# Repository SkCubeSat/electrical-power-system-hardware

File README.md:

# electrical-power-system-hardware

see branch 'master' for hardware design files

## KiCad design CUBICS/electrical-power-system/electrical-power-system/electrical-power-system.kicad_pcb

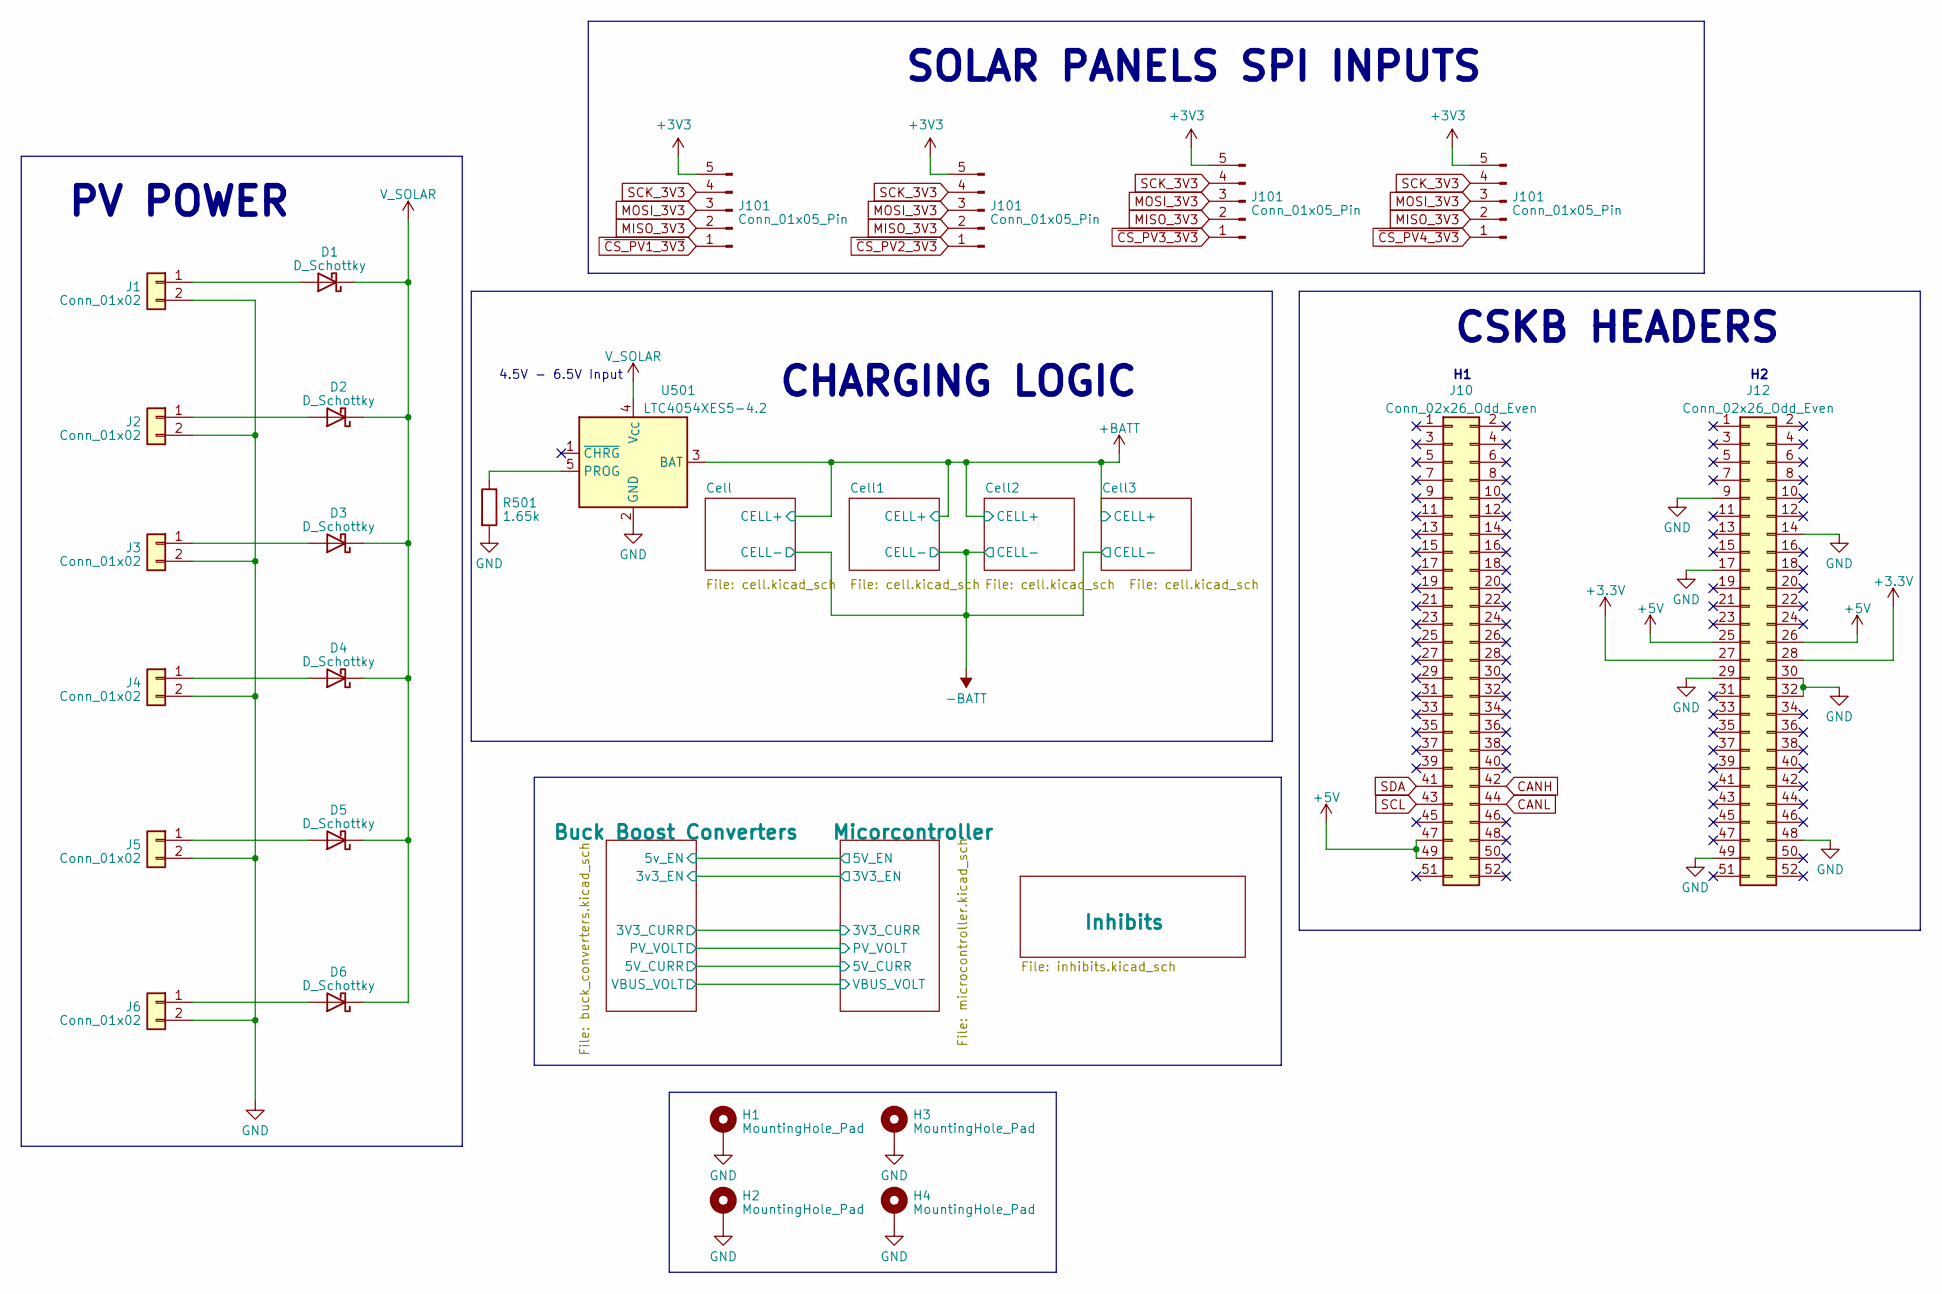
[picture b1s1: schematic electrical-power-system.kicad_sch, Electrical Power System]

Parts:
D1, D2, D3, D4, D5, D6: D_Schottky; D_A-405_P10.16mm_Horizontal
H1, H2, H3, H4: MountingHole_Pad; MountingHole_3.2mm_M3_ISO7380_Pad_TopBottom
J1, J2, J3, J4, J5, J6: Conn_01x02; PinHeader_1x02_P2.54mm_Vertical
J10, J12: Conn_02x26_Odd_Even; PinSocket_2x26_P2.54mm_Vertical
J101: Conn_01x05_Pin; Hirose_DF13-05P-1.25DSA_1x05_P1.25mm_Vertical
R501: 1.65k; R_0603_1608Metric
U501: LTC4054XES5-4.2; TSOT-23-5

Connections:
+1V2: D1.1 (K), D2.1 (K), D3.1 (K), D4.1 (K), D5.1 (K), D6.1 (K); also elsewhere on the board
+3.3V: J12.27, J12.28; also elsewhere on the board
+5V: J10.47, J10.49, J12.25, J12.26; also elsewhere on the board
CANH: J10.42; also elsewhere on the board
CANL: J10.44; also elsewhere on the board
GND: H1.1, H2.1, H3.1, H4.1, J1.2, J2.2, J3.2, J4.2, J5.2, J6.2, J12.9, J12.14, J12.17, J12.29, J12.30, J12.32, J12.48, J12.49; also elsewhere on the board
unnamed: D1.2 (A), J1.1
unnamed: D2.2 (A), J2.1
unnamed: D3.2 (A), J3.1
unnamed: D4.2 (A), J4.1
unnamed: D5.2 (A), J5.1
unnamed: D6.2 (A), J6.1
SCL: J10.43; also elsewhere on the board
SDA: J10.41; also elsewhere on the board

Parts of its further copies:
J7, J8, J9, J11: Conn_01x05_Pin; Hirose_DF13-05P-1.25DSA_1x05_P1.25mm_Vertical
R1: 1.65k; R_0603_1608Metric
U1: LTC4054XES5-4.2; TSOT-23-5

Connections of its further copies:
+1V2: U1.4 (V_{CC}); also elsewhere on the board
+3V3: J7.5, J8.5, J9.5, J11.5; also elsewhere on the board
+BATT: U1.3 (BAT); also elsewhere on the board
GND: R1.2, U1.2 (GND); also elsewhere on the board
MISO_3V3: J7.2, J8.2, J9.2, J11.2; also elsewhere on the board
MOSI_3V3: J7.3, J8.3, J9.3, J11.3; also elsewhere on the board
unnamed: R1.1, U1.5 (PROG)
SCK_3V3: J7.4, J8.4, J9.4, J11.4; also elsewhere on the board
~CS_PV1_3V3: J7.1; also elsewhere on the board
~CS_PV2_3V3: J8.1; also elsewhere on the board
~CS_PV3_3V3: J9.1; also elsewhere on the board
~CS_PV4_3V3: J11.1; also elsewhere on the board

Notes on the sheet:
PV POWER
CSKB HEADERS
4.5V - 6.5V Input
SOLAR PANELS SPI INPUTS
CHARGING LOGIC

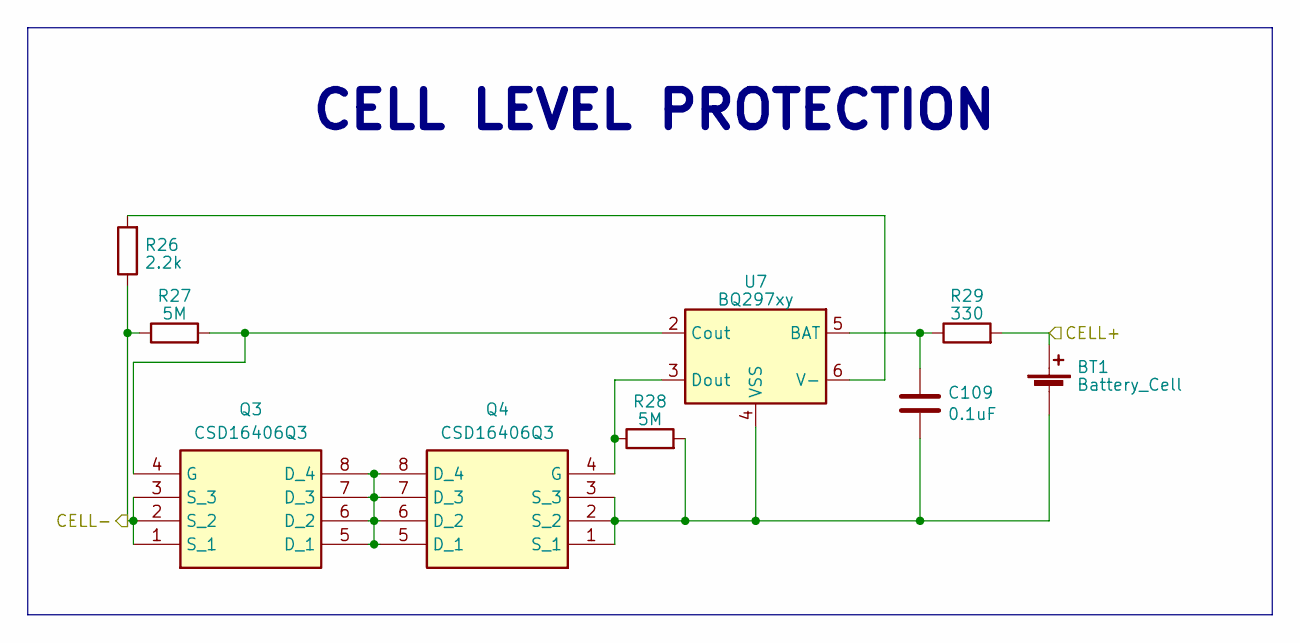
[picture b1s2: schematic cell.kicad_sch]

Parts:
BT1: Battery_Cell; 18650_TH
C109: 0.1uF; C_0603_1608Metric
Q3, Q4: CSD16406Q3; DQG_VSON-CLIP; Manufacturer_Part_Number CSD16406Q3; Mouser Part Number 595-CSD16406Q3
R26: 2.2k; R_0603_1608Metric
R27, R28: 5M; R_0603_1608Metric
R29: 330; R_0603_1608Metric
U7: BQ297xy; WSON-6_1.5x1.5mm_P0.5mm

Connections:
+BATT: BT1.1 (+), R29.2; also elsewhere on the board
-BATT: Q3.1 (S_1), Q3.2 (S_2), Q3.3 (S_3), R26.1, R27.1; also elsewhere on the board
unnamed 19: BT1.2 (-), Q4.1 (S_1), Q4.2 (S_2), Q4.3 (S_3), R28.2, U7.4 (VSS); also elsewhere on the board
unnamed: Q3.5 (D_1), Q3.6 (D_2), Q3.7 (D_3), Q3.8 (D_4), Q4.5 (D_1), Q4.6 (D_2), Q4.7 (D_3), Q4.8 (D_4)
unnamed: Q3.4 (G), R27.2, U7.2 (Cout)
unnamed: Q4.4 (G), R28.1, U7.3 (Dout)
unnamed 73: R29.1, U7.5 (BAT); also elsewhere on the board
unnamed: R26.2, U7.6 (V-)

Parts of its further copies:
BT2, BT3, BT4: Battery_Cell; 18650_TH
C25, C26, C27, C28: 0.1uF; C_0603_1608Metric
Q5, Q6, Q7, Q8, Q9, Q10: CSD16406Q3; DQG_VSON-CLIP; Manufacturer_Part_Number CSD16406Q3; Mouser Part Number 595-CSD16406Q3
R30, R34, R38: 2.2k; R_0603_1608Metric
R31, R32, R35, R36, R39, R40: 5M; R_0603_1608Metric
R33, R37, R41: 330; R_0603_1608Metric
U8, U9, U10: BQ297xy; WSON-6_1.5x1.5mm_P0.5mm

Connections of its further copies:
+BATT: BT2.1 (+), BT3.1 (+), BT4.1 (+), R33.2, R37.2, R41.2; also elsewhere on the board
-BATT: Q5.1 (S_1), Q5.2 (S_2), Q5.3 (S_3), Q7.1 (S_1), Q7.2 (S_2), Q7.3 (S_3), Q9.1 (S_1), Q9.2 (S_2), Q9.3 (S_3), R30.1, R31.1, R34.1, R35.1, R38.1, R39.1; also elsewhere on the board
unnamed 19: C25.2; also elsewhere on the board
unnamed: BT2.2 (-), C26.2, Q6.1 (S_1), Q6.2 (S_2), Q6.3 (S_3), R32.2, U8.4 (VSS)
unnamed: BT3.2 (-), C27.2, Q8.1 (S_1), Q8.2 (S_2), Q8.3 (S_3), R36.2, U9.4 (VSS)
unnamed: BT4.2 (-), C28.2, Q10.1 (S_1), Q10.2 (S_2), Q10.3 (S_3), R40.2, U10.4 (VSS)
unnamed: Q5.5 (D_1), Q5.6 (D_2), Q5.7 (D_3), Q5.8 (D_4), Q6.5 (D_1), Q6.6 (D_2), Q6.7 (D_3), Q6.8 (D_4)
unnamed: Q5.4 (G), R31.2, U8.2 (Cout)
unnamed: Q6.4 (G), R32.1, U8.3 (Dout)
unnamed: Q7.5 (D_1), Q7.6 (D_2), Q7.7 (D_3), Q7.8 (D_4), Q8.5 (D_1), Q8.6 (D_2), Q8.7 (D_3), Q8.8 (D_4)
unnamed: Q7.4 (G), R35.2, U9.2 (Cout)
unnamed: Q8.4 (G), R36.1, U9.3 (Dout)
unnamed: Q9.4 (G), R39.2, U10.2 (Cout)
unnamed: Q9.5 (D_1), Q9.6 (D_2), Q9.7 (D_3), Q9.8 (D_4), Q10.5 (D_1), Q10.6 (D_2), Q10.7 (D_3), Q10.8 (D_4)
unnamed: Q10.4 (G), R40.1, U10.3 (Dout)
unnamed 73: C25.1; also elsewhere on the board
unnamed: C26.1, R33.1, U8.5 (BAT)
unnamed: R30.2, U8.6 (V-)
unnamed: C27.1, R37.1, U9.5 (BAT)
unnamed: R34.2, U9.6 (V-)
unnamed: C28.1, R41.1, U10.5 (BAT)
unnamed: R38.2, U10.6 (V-)

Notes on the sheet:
CELL LEVEL PROTECTION

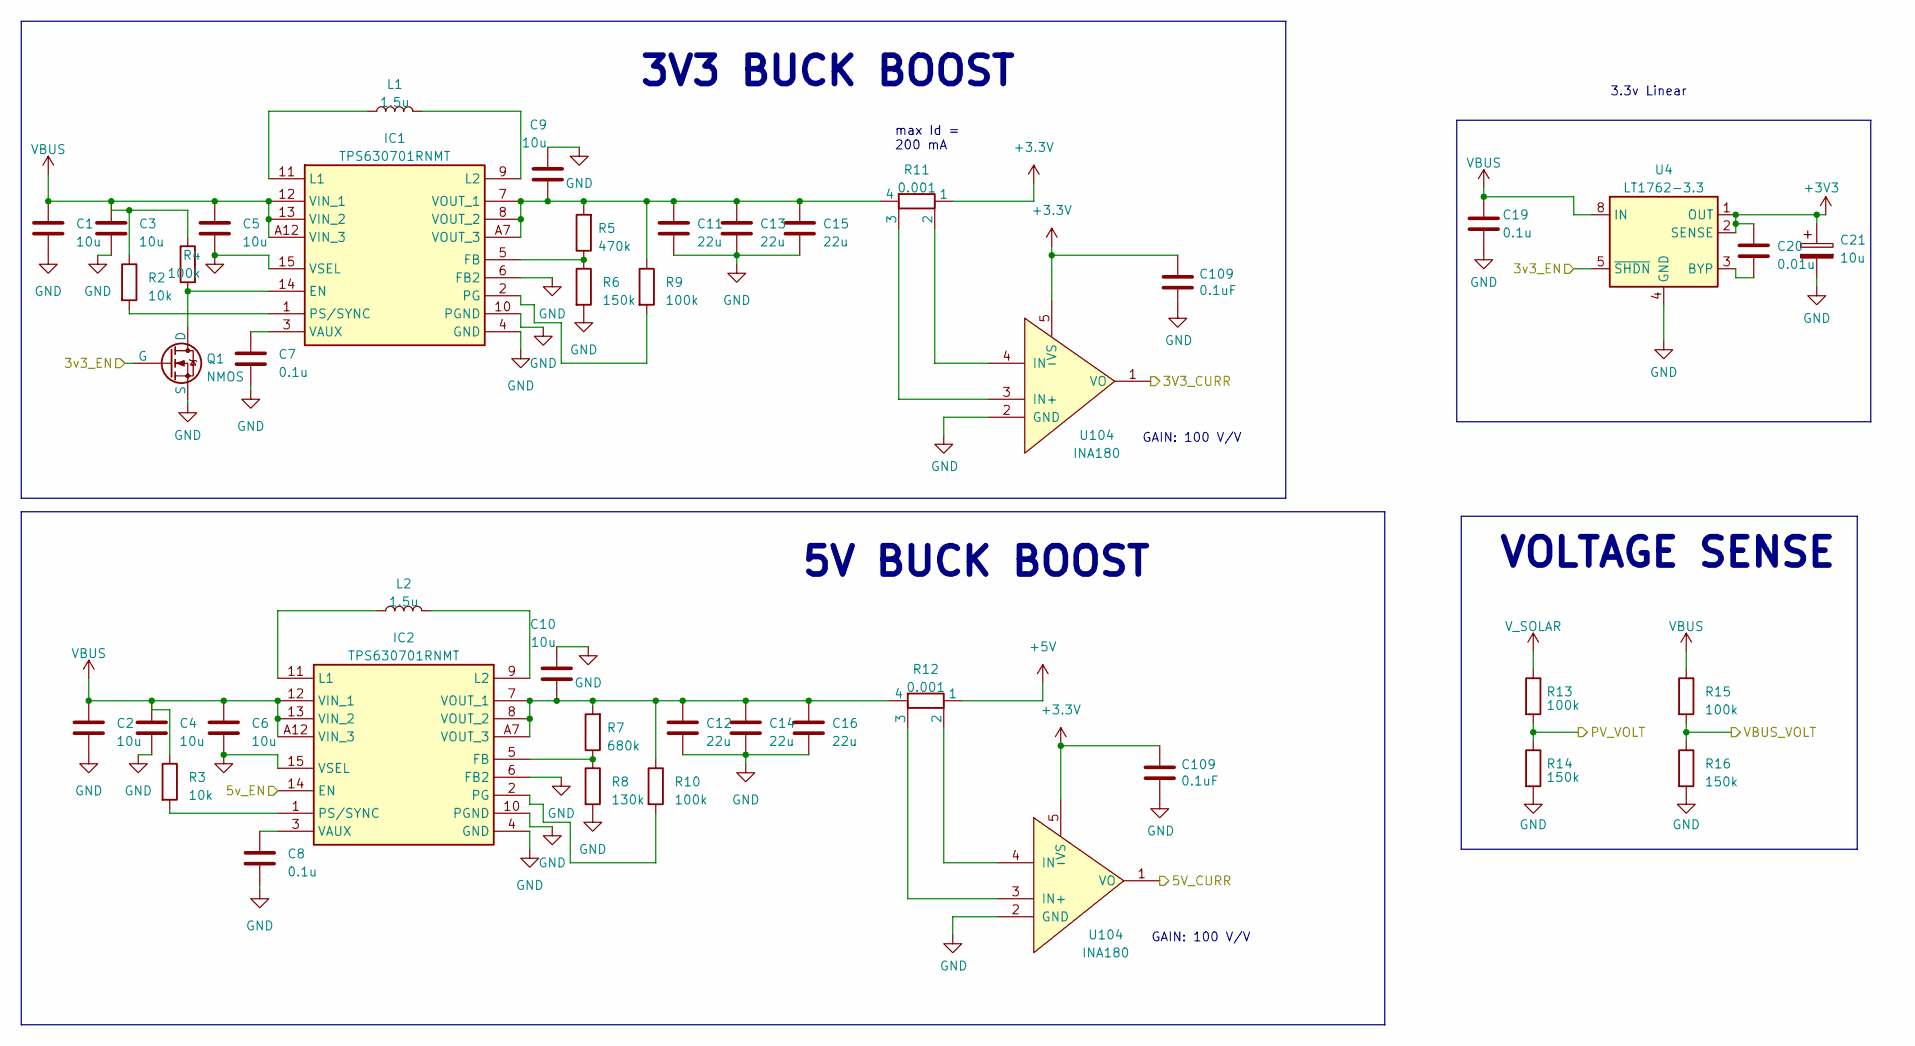
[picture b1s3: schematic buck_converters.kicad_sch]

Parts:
C1, C2, C3, C4: 10u; C_0805_2012Metric
C5, C6, C9, C10: 10u; C_0603_1608Metric
C7, C8: 0.1u; C_0402_1005Metric
C11, C12, C13, C14, C15, C16: 22u; C_0805_2012Metric
C19: 0.1u; C_0603_1608Metric
C20: 0.01u; C_0402_1005Metric
C21: 10u; CP_Radial_D4.0mm_P1.50mm
C109: 0.1uF; C_0603_1608Metric
IC1, IC2: TPS630701RNMT; Manufacturer_Part_Number TPS630701RNMT; Mouser Part Number 595-TPS630701RNMT
L1, L2: 1.5u; L_Bourns-SRN4018
Q1: NMOS; SOT-23-3
R2, R3: 10k; R_0603_1608Metric
R4, R9, R10, R13, R15: 100k; R_0603_1608Metric
R5: 470k; R_0603_1608Metric
R6, R14, R16: 150k; R_0603_1608Metric
R7: 680k; R_0603_1608Metric
R8: 130k; R_0603_1608Metric
R11, R12: 0.001; WSL27261L000FEA
U4: LT1762-3.3; MSOP-8_3x3mm_P0.65mm
U104: INA180; SOT-23-5_HandSoldering

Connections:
+1V2: R13.1; also elsewhere on the board
+3.3V: R11.1; also elsewhere on the board
+3V3: C20.1, C21.1, U4.1 (OUT), U4.2 (SENSE); also elsewhere on the board
+5V: R12.1; also elsewhere on the board
/Buck Boost Converters/3v3_EN: Q1.2 (G), U4.5 (~SHDN); also elsewhere on the board
/Buck Boost Converters/5v_EN: IC2.14 (EN); also elsewhere on the board
/Buck Boost Converters/PV_VOLT: R13.2, R14.1; also elsewhere on the board
/Buck Boost Converters/VBUS_VOLT: R15.2, R16.1; also elsewhere on the board
GND: C1.2, C2.2, C3.2, C4.2, C5.2, C6.2, C7.2, C8.2, C9.2, C10.2, C11.2, C12.2, C13.2, C14.2, C15.2, C16.2, C19.2, C21.2, IC1.4 (GND), IC1.6 (FB2), IC1.10 (PGND), IC1.15 (VSEL), IC2.4 (GND), IC2.6 (FB2), IC2.10 (PGND), IC2.15 (VSEL), Q1.3 (S), R6.2, R8.2, R14.2, R16.2, U4.4 (GND); also elsewhere on the board
unnamed: IC1.14 (EN), Q1.1 (D), R4.2
unnamed: IC1.5 (FB), R5.1, R6.1
unnamed: IC1.11 (L1), L1.1
unnamed: IC1.9 (L2), L1.2
unnamed: IC1.2 (PG), R9.2
unnamed: IC1.1 (PS/SYNC), R2.2
unnamed: C7.1, IC1.3 (VAUX)
unnamed: C9.1, C11.1, C13.1, C15.1, IC1.7 (VOUT_1), IC1.8 (VOUT_2), IC1.A7 (VOUT_3), R5.2, R9.1, R11.4
unnamed: IC2.5 (FB), R7.1, R8.1
unnamed: IC2.11 (L1), L2.1
unnamed: IC2.9 (L2), L2.2
unnamed: IC2.2 (PG), R10.2
unnamed: IC2.1 (PS/SYNC), R3.2
unnamed: C8.1, IC2.3 (VAUX)
unnamed: C10.1, C12.1, C14.1, C16.1, IC2.7 (VOUT_1), IC2.8 (VOUT_2), IC2.A7 (VOUT_3), R7.2, R10.1, R12.4
unnamed 64: R11.3; also elsewhere on the board
unnamed 65: R11.2; also elsewhere on the board
unnamed 66: R12.3; also elsewhere on the board
unnamed 67: R12.2; also elsewhere on the board
unnamed: C20.2, U4.3 (BYP)
VBUS: C1.1, C2.1, C3.1, C4.1, C5.1, C6.1, C19.1, IC1.12 (VIN_1), IC1.13 (VIN_2), IC1.A12 (VIN_3), IC2.12 (VIN_1), IC2.13 (VIN_2), IC2.A12 (VIN_3), R2.1, R3.1, R4.1, R15.1, U4.8 (IN); also elsewhere on the board

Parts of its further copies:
C17, C18: 0.1uF; C_0603_1608Metric
U2, U3: INA180; SOT-23-5_HandSoldering

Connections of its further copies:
+3.3V: C17.1, C18.1, U2.5 (VS), U3.5 (VS); also elsewhere on the board
/Buck Boost Converters/3V3_CURR: U2.1 (VO); also elsewhere on the board
/Buck Boost Converters/5V_CURR: U3.1 (VO); also elsewhere on the board
GND: C17.2, C18.2, U2.2 (GND), U3.2 (GND); also elsewhere on the board
unnamed 64: U2.3 (IN+); also elsewhere on the board
unnamed 65: U2.4 (IN-); also elsewhere on the board
unnamed 66: U3.3 (IN+); also elsewhere on the board
unnamed 67: U3.4 (IN-); also elsewhere on the board

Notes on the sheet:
5V BUCK BOOST
VOLTAGE SENSE
3.3v Linear
GAIN: 100 V/V
3V3 BUCK BOOST
max Id = 200 mA

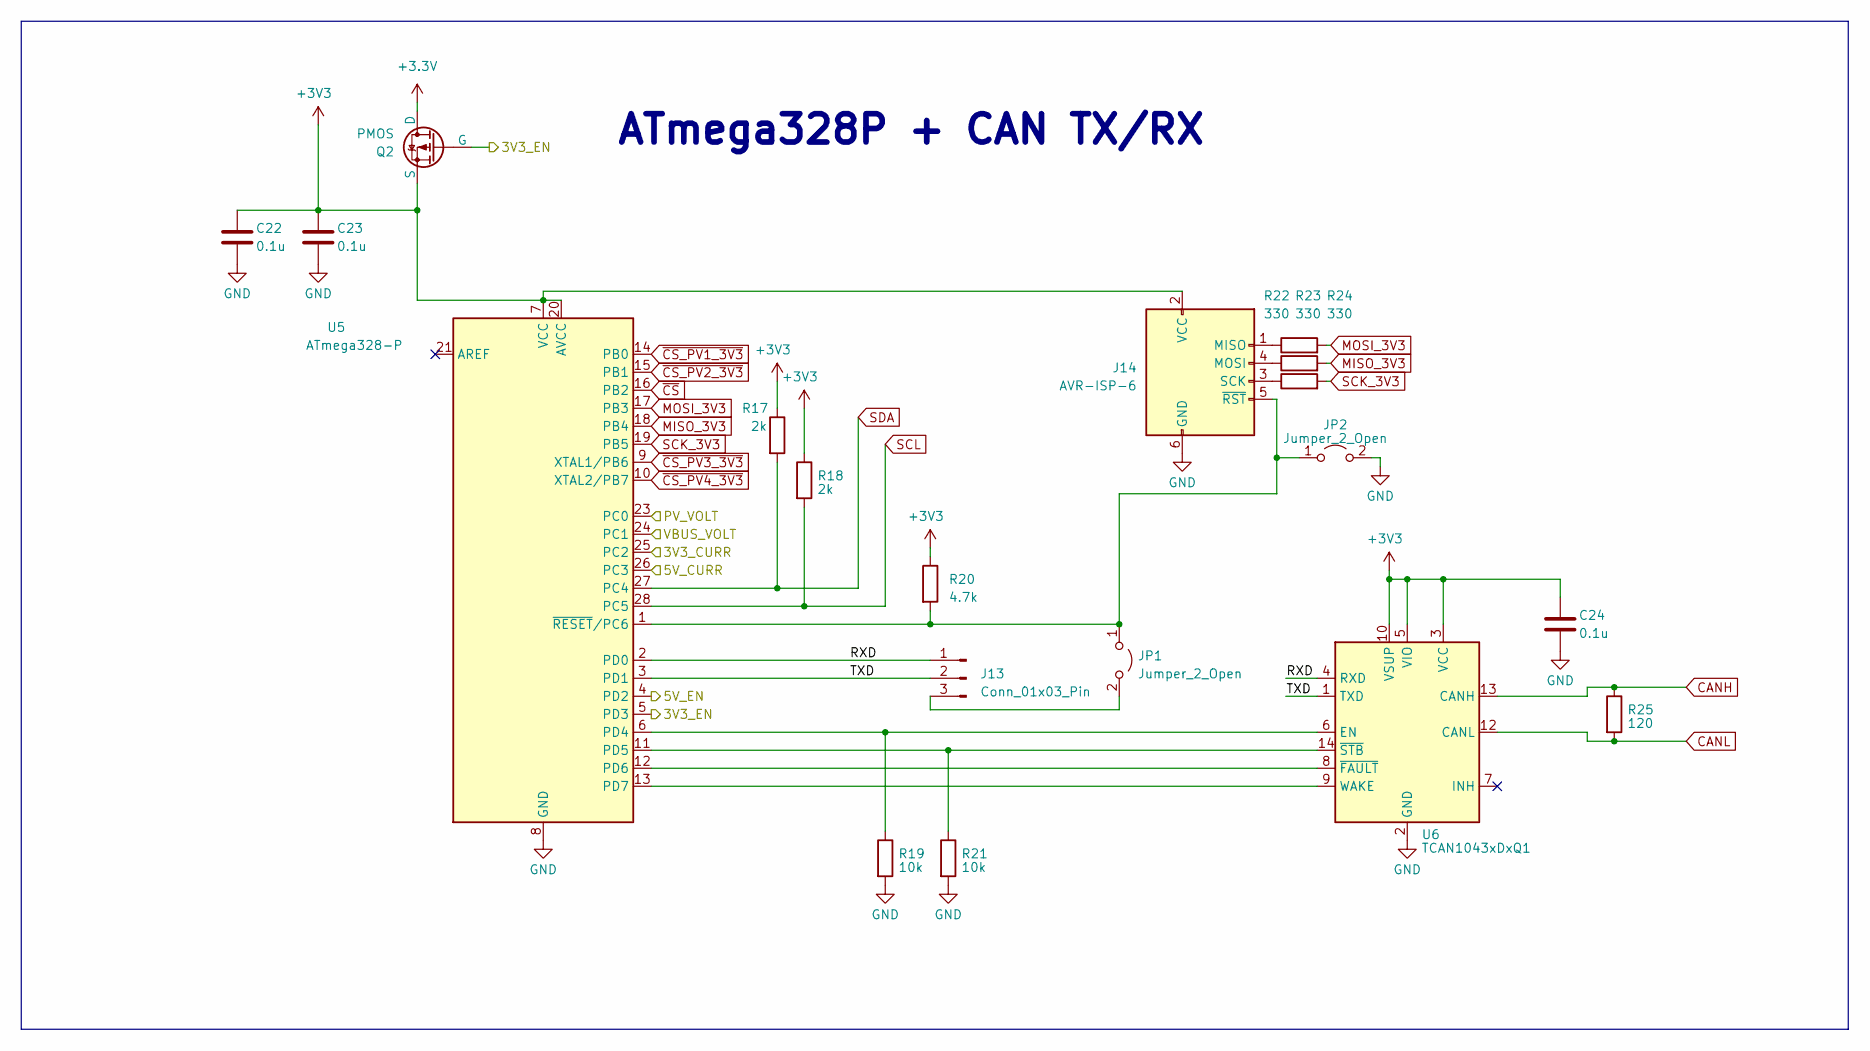
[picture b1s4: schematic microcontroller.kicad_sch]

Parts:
C22, C23, C24: 0.1u; C_0603_1608Metric
J13: Conn_01x03_Pin; PinHeader_1x03_P2.54mm_Vertical
J14: AVR-ISP-6; PinHeader_2x03_P2.54mm_Vertical
JP1, JP2: Jumper_2_Open; R_0603_1608Metric
Q2: PMOS; SOT-23
R17, R18: 2k; R_0603_1608Metric
R19, R21: 10k; R_0603_1608Metric
R20: 4.7k; R_0603_1608Metric
R22, R23, R24: 330; R_0603_1608Metric
R25: 120; R_0603_1608Metric
U5: ATmega328-P; DIP-28_W7.62mm
U6: TCAN1043xDxQ1; SOIC-14_3.9x8.7mm_P1.27mm

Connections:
+3.3V: Q2.1 (D); also elsewhere on the board
+3V3: C22.1, C23.1, C24.1, J14.2 (VCC), Q2.3 (S), R17.1, R18.1, R20.1, U5.7 (VCC), U5.20 (AVCC), U6.3 (VCC), U6.5 (VIO), U6.10 (VSUP); also elsewhere on the board
/Buck Boost Converters/3V3_CURR: U5.25 (PC2); also elsewhere on the board
/Buck Boost Converters/3v3_EN: Q2.2 (G), U5.5 (PD3); also elsewhere on the board
/Buck Boost Converters/5V_CURR: U5.26 (PC3); also elsewhere on the board
/Buck Boost Converters/5v_EN: U5.4 (PD2); also elsewhere on the board
/Buck Boost Converters/PV_VOLT: U5.23 (PC0); also elsewhere on the board
/Buck Boost Converters/VBUS_VOLT: U5.24 (PC1); also elsewhere on the board
/Micorcontroller/RXD: J13.1, U5.2 (PD0), U6.4 (RXD)
/Micorcontroller/TXD: J13.2, U5.3 (PD1), U6.1 (TXD)
CANH: R25.1, U6.13 (CANH); also elsewhere on the board
CANL: R25.2, U6.12 (CANL); also elsewhere on the board
GND: C22.2, C23.2, C24.2, J14.6 (GND), JP2.2 (B), R19.2, R21.2, U5.8 (GND), U5.22 (GND), U6.2 (GND); also elsewhere on the board
MISO_3V3: R23.2, U5.18 (PB4); also elsewhere on the board
MOSI_3V3: R22.2, U5.17 (PB3); also elsewhere on the board
unnamed: J13.3, JP1.2 (B)
unnamed: J14.1 (MISO), R22.1
unnamed: J14.4 (MOSI), R23.1
unnamed: J14.3 (SCK), R24.1
unnamed: J14.5 (~RST), JP1.1 (A), JP2.1 (A), R20.2, U5.1 (~RESET/PC6)
unnamed: R19.1, U5.6 (PD4), U6.6 (EN)
unnamed: R21.1, U5.11 (PD5), U6.14 (~STB)
unnamed: U5.12 (PD6), U6.8 (~FAULT)
unnamed: U5.13 (PD7), U6.9 (WAKE)
SCK_3V3: R24.2, U5.19 (PB5); also elsewhere on the board
SCL: R18.2, U5.28 (PC5); also elsewhere on the board
SDA: R17.2, U5.27 (PC4); also elsewhere on the board
~CS_PV1_3V3: U5.14 (PB0); also elsewhere on the board
~CS_PV2_3V3: U5.15 (PB1); also elsewhere on the board
~CS_PV3_3V3: U5.9 (XTAL1/PB6); also elsewhere on the board
~CS_PV4_3V3: U5.10 (XTAL2/PB7); also elsewhere on the board
~CS: U5.16 (PB2)

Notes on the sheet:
ATmega328P + CAN TX/RX

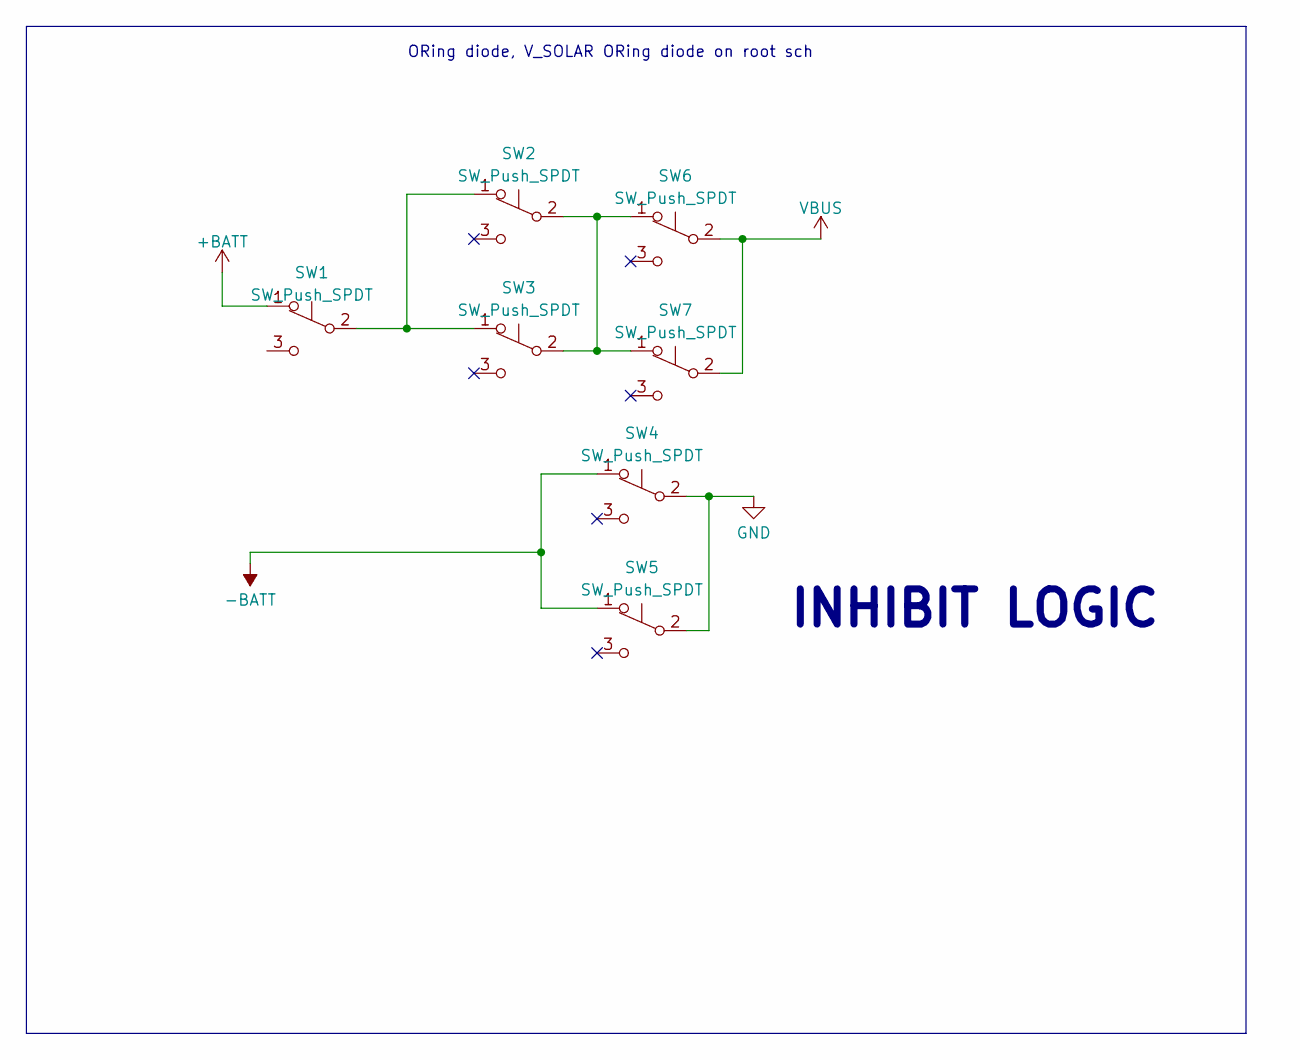
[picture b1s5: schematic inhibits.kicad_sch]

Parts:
SW1: SW_Push_SPDT; PinHeader_1x03_P2.54mm_Vertical
SW2, SW3, SW4, SW5, SW6, SW7: SW_Push_SPDT; PinHeader_1x02_P2.54mm_Vertical

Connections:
+BATT: SW1.1 (A); also elsewhere on the board
-BATT: SW4.1 (A), SW5.1 (A); also elsewhere on the board
GND: SW4.2 (B), SW5.2 (B); also elsewhere on the board
unnamed: SW1.2 (B), SW2.1 (A), SW3.1 (A)
unnamed: SW2.2 (B), SW3.2 (B), SW6.1 (A), SW7.1 (A)
VBUS: SW6.2 (B), SW7.2 (B); also elsewhere on the board

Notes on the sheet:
ORing diode, V_SOLAR ORing diode on root sch
INHIBIT LOGIC

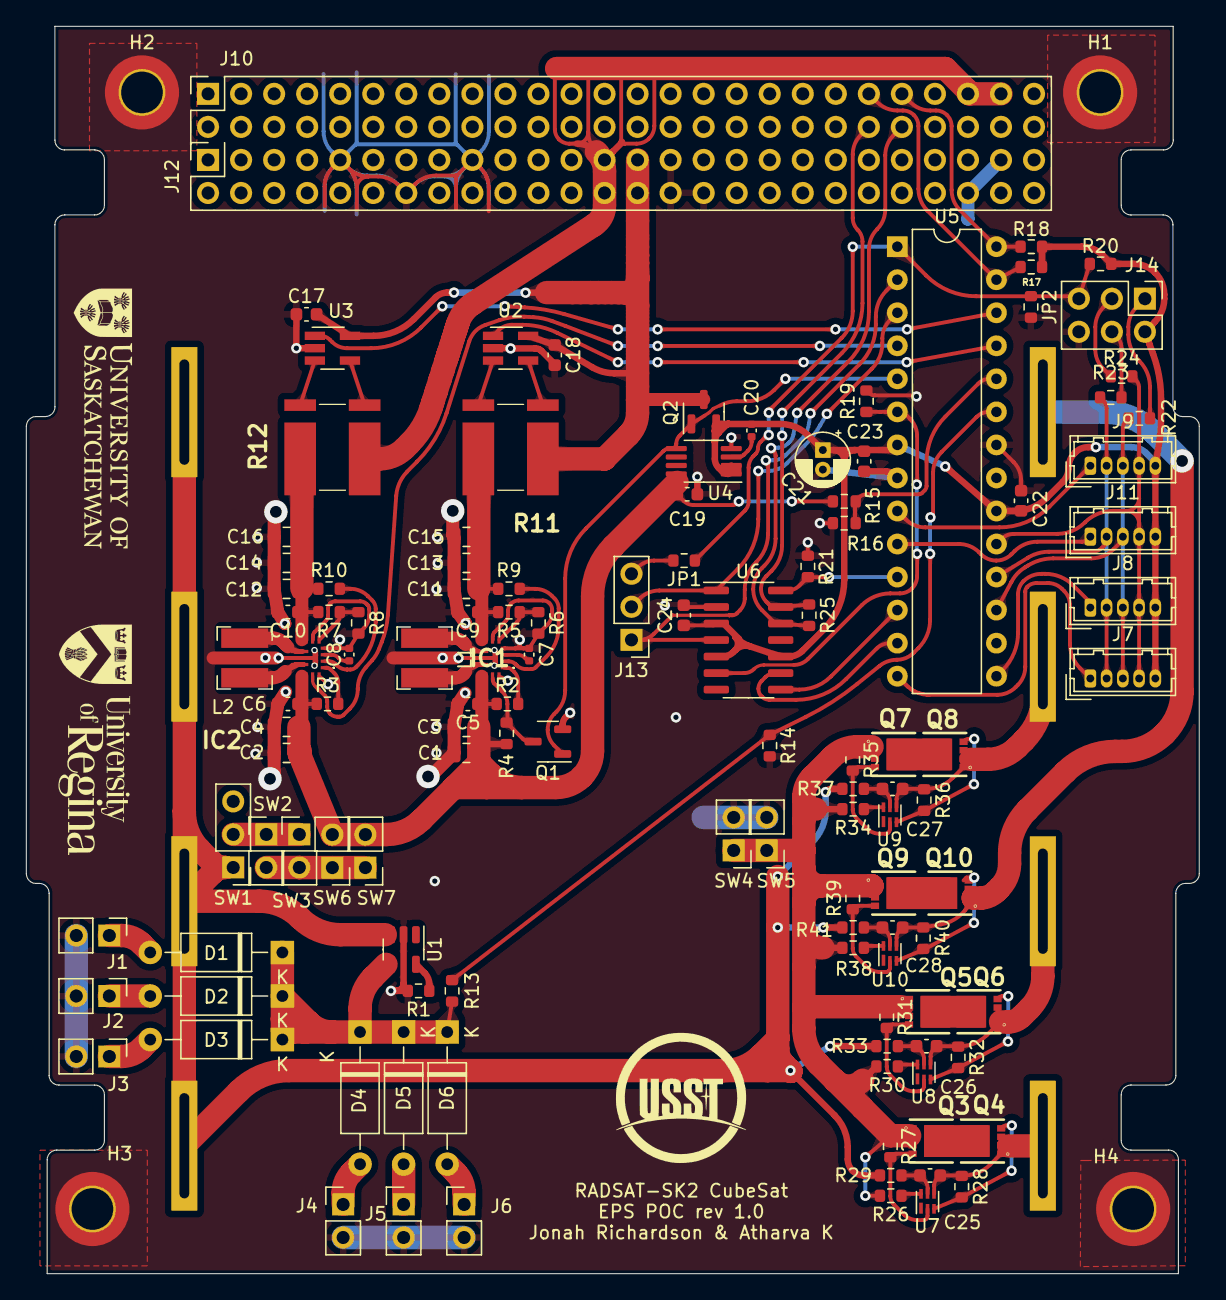
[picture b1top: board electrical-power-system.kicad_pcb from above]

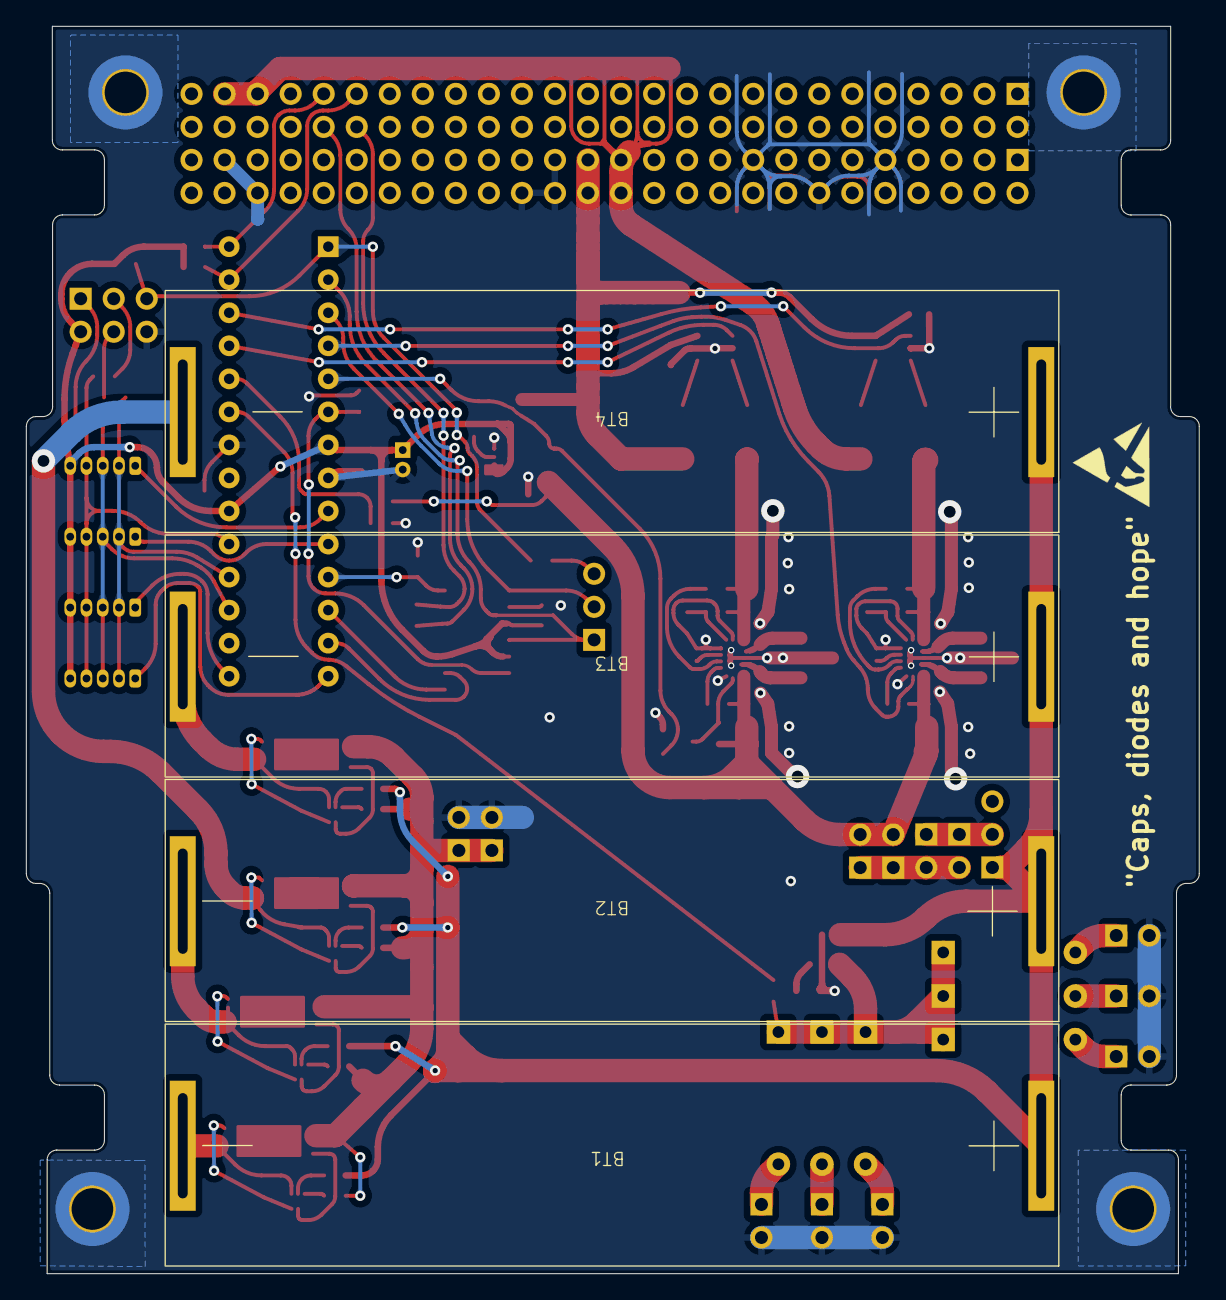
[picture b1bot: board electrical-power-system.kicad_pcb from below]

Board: 2 copper layers, 90.2 x 95.9 mm, 130 parts (4 on the bottom side), 89 nets.

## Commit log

2023-07-10 kicad init
2023-07-10 branch name test
2023-07-10 deleted test to test lol
2023-07-10 schematic v1.0
2023-07-23 rev 1.0 routing complete updated schematic
2023-07-24 Added thermal relief pads to ground plane
2023-07-25 push for production
